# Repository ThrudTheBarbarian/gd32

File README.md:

# gd32
Test board for the GD32F450 cpu

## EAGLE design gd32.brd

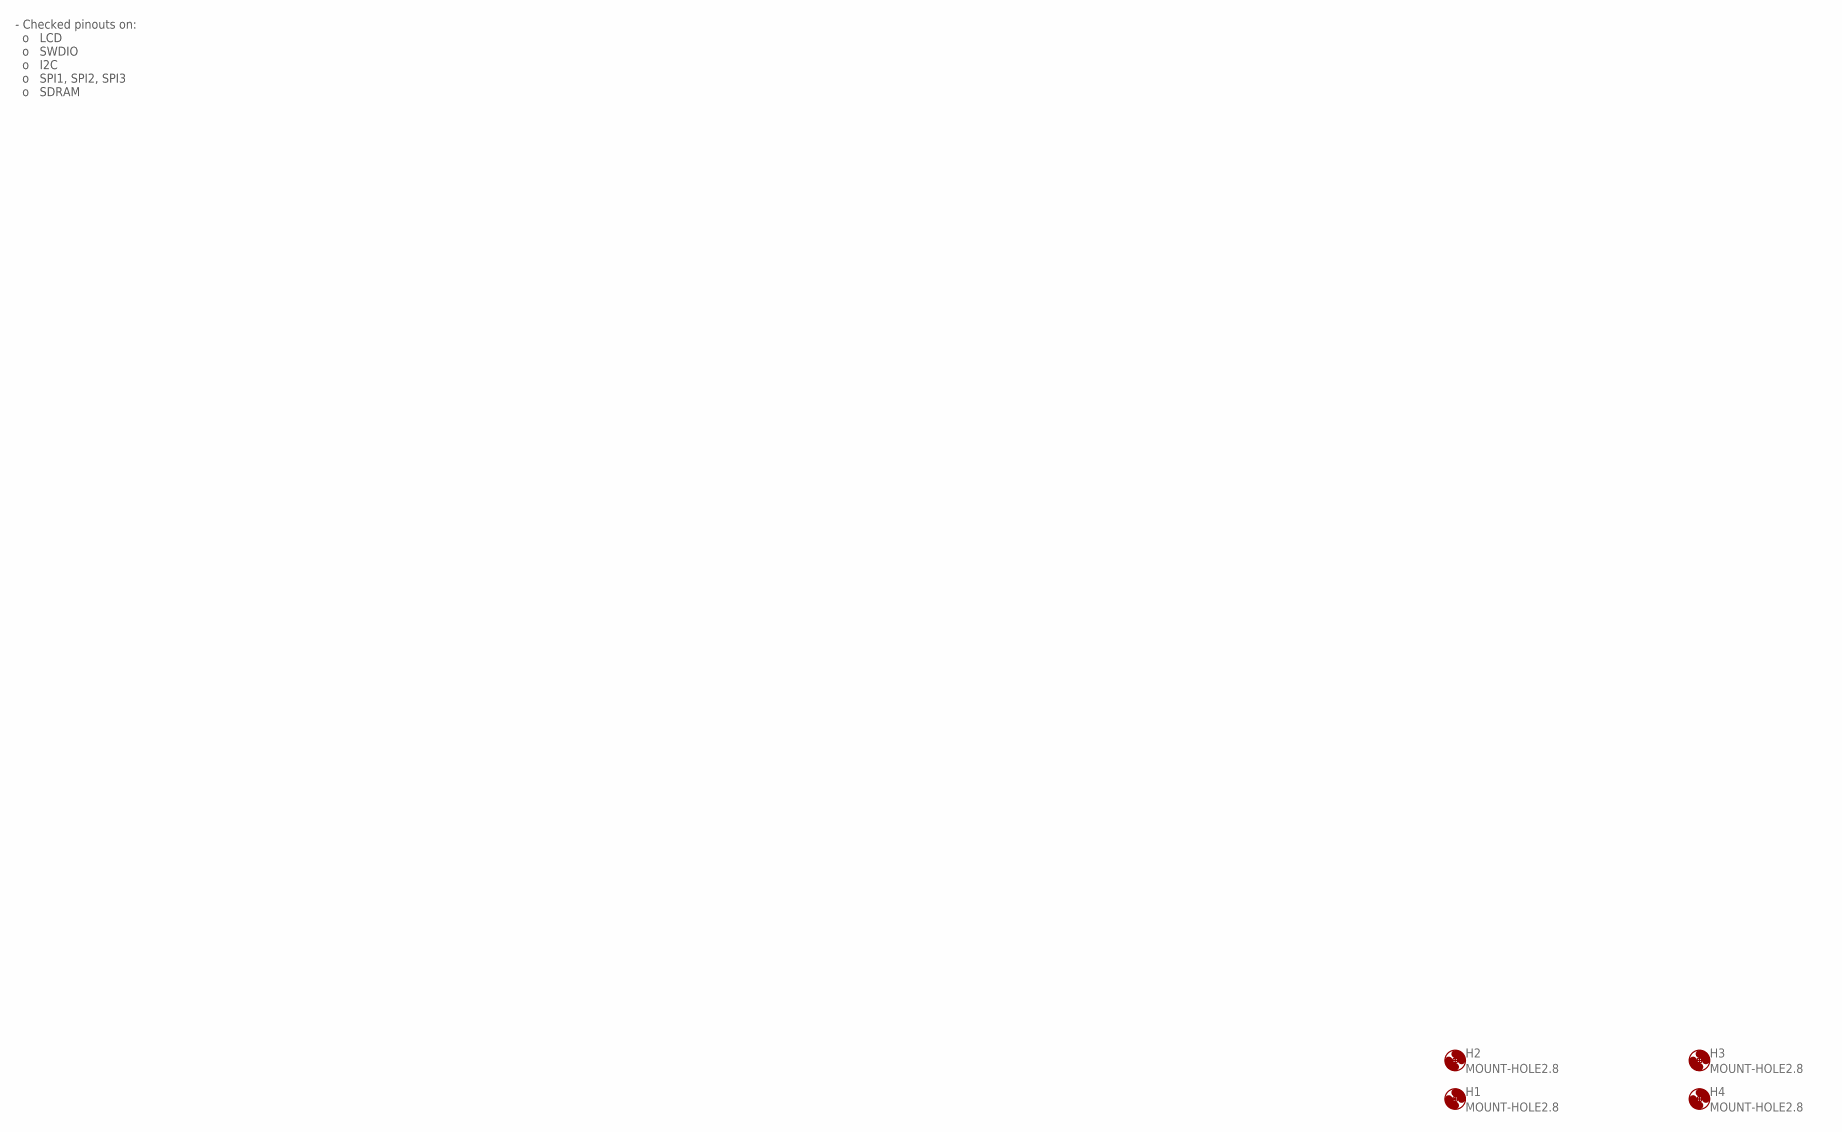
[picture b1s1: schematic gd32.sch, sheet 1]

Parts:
H1, H2, H3, H4: MOUNT-HOLE2.8; 2,8

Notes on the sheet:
- Checked pinouts on: o LCD o SWDIO o I2C o SPI1, SPI2, SPI3 o SDRAM

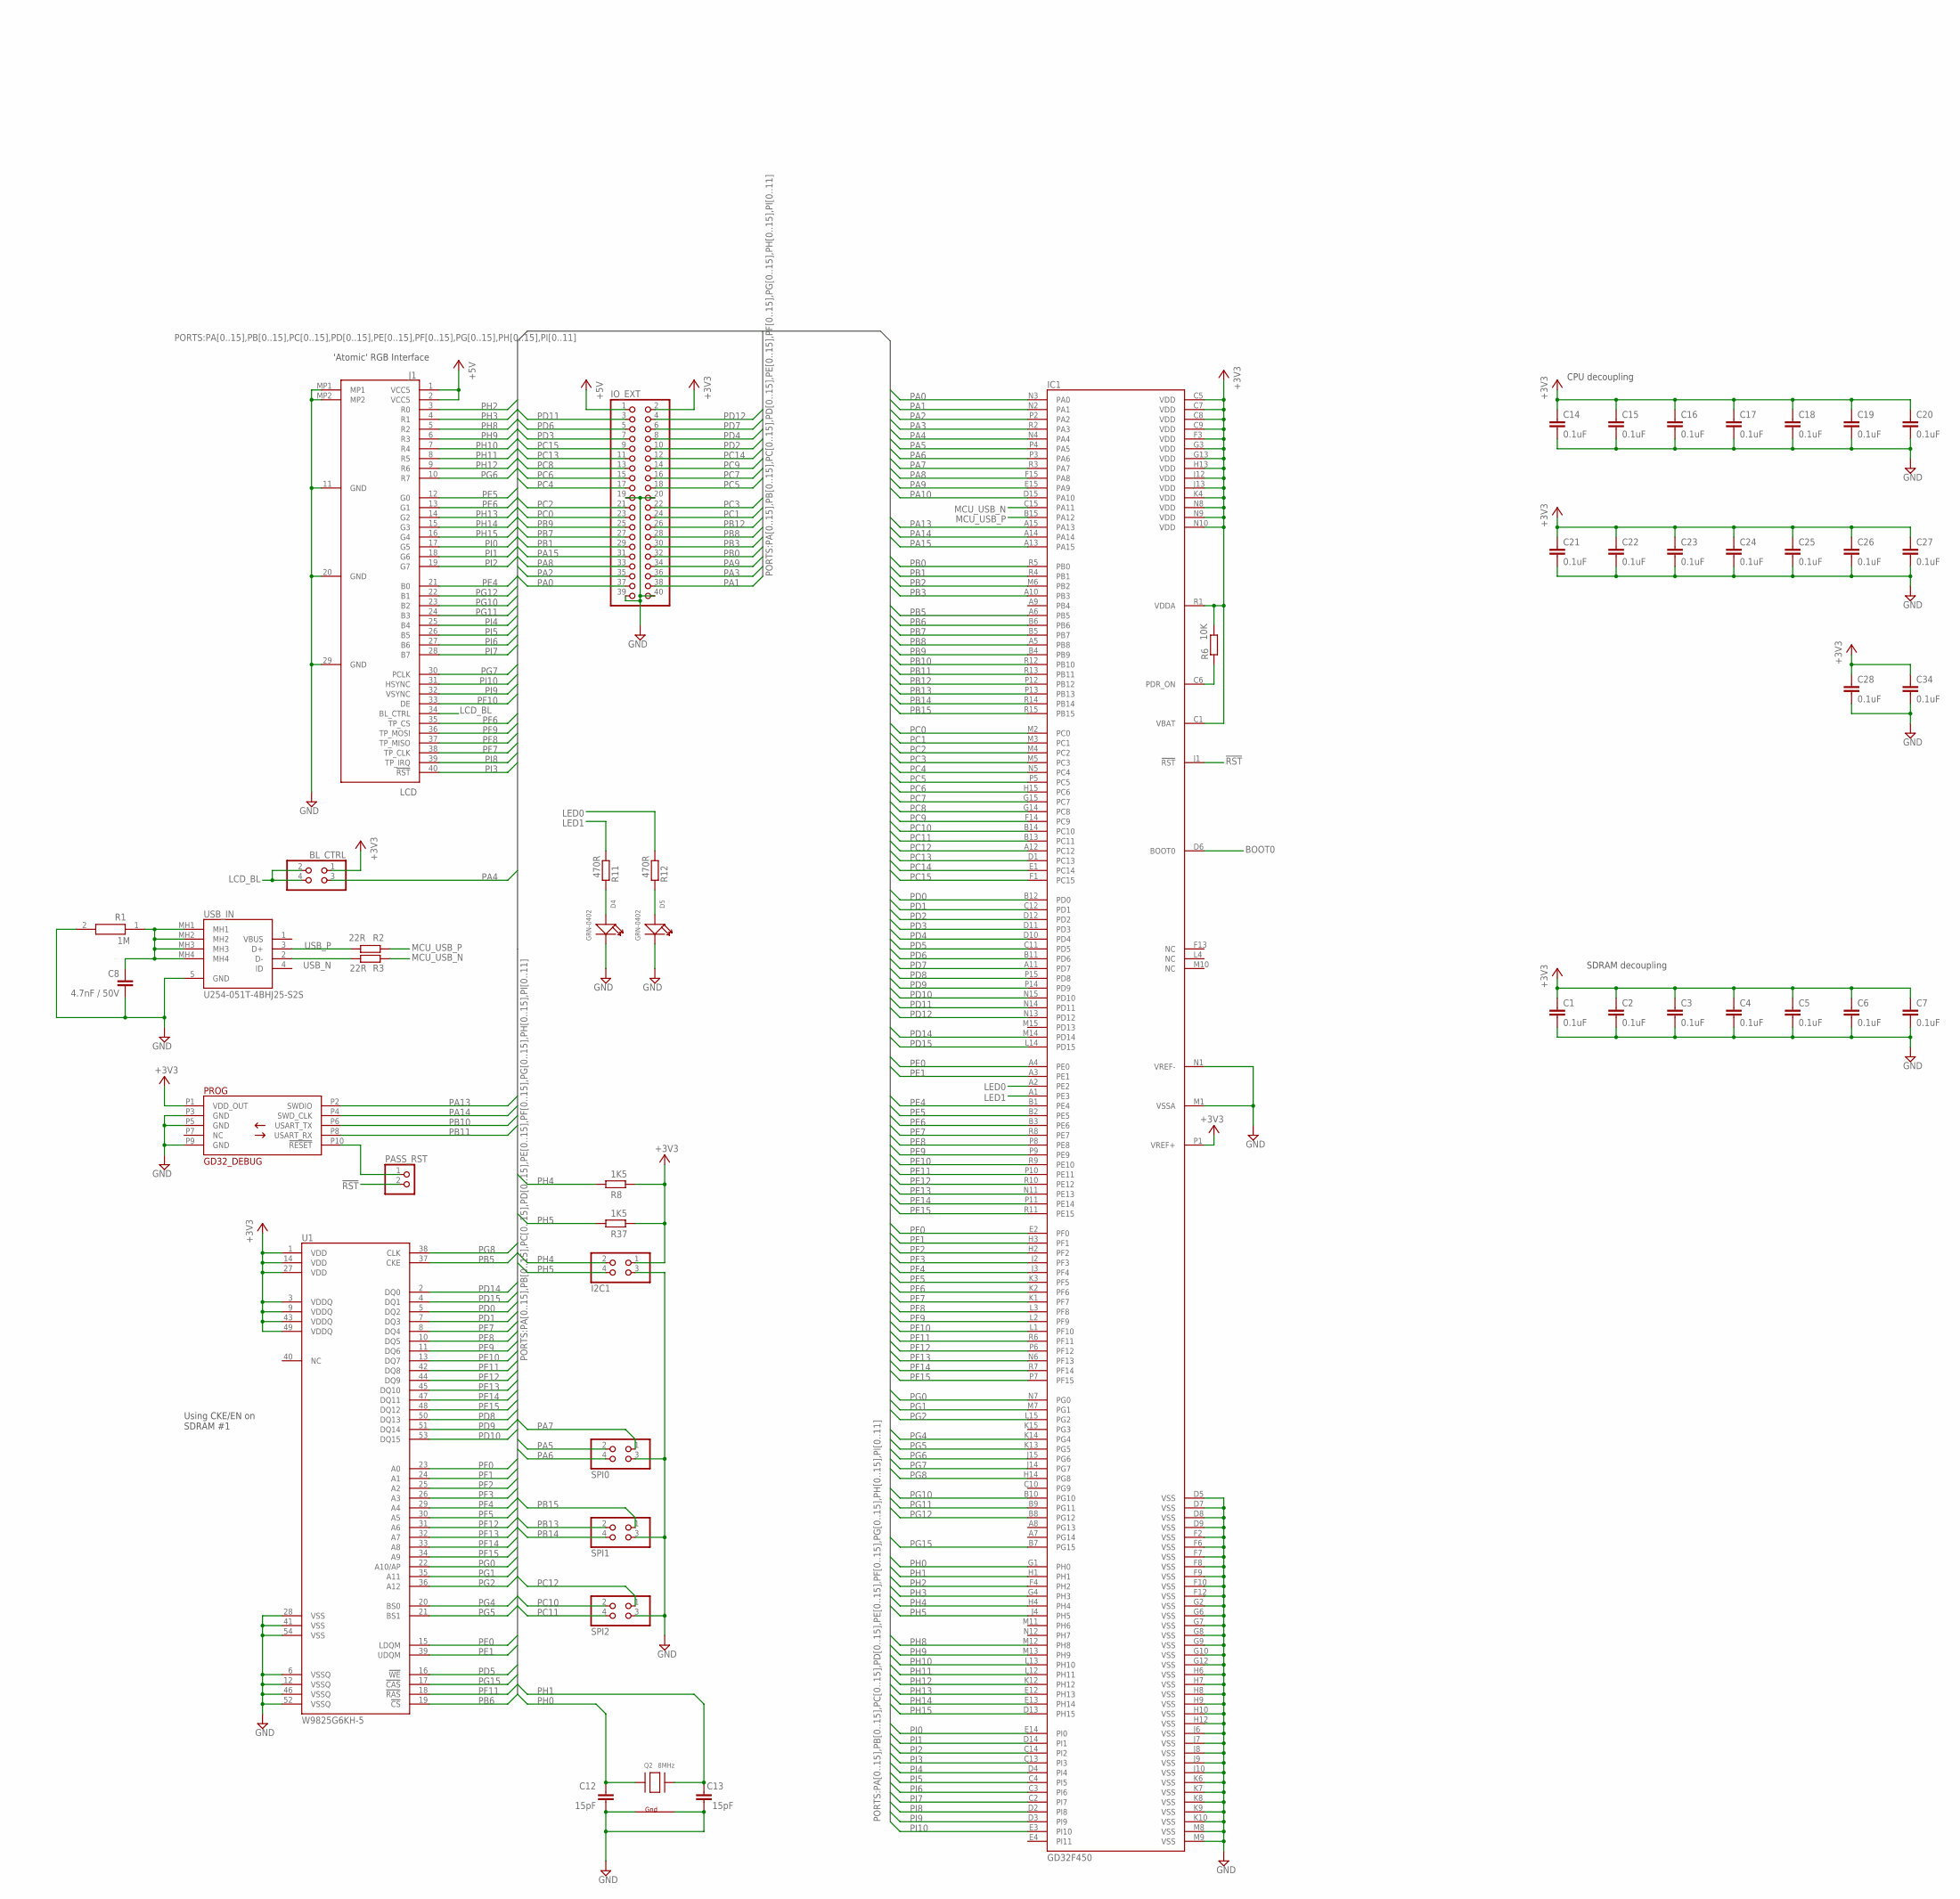
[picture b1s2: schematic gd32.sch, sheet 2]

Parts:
BL_CTRL: PINHD-2X2; 2X02
C1, C2, C3, C4, C5, C6, C7, C14, C15, C16, C17, C18, C19, C20, C21, C22, C23, C24, C25, C26, C27, C28, C34: 0.1uF; C0201
C8: 4.7nF / 50V; C0201
C12, C13: 15pF; C0201
D4, D5: GRN-0402; LED-0402
I2C1: PINHD-2X2; 2X02
IC1: GD32F450; BGA201C65P15X15_1000X1000X84
IO_EXT: PINHD-2X20; 2X20
J1: LCD; CF5040FD0R005NH
PASS_RST: PINHD-1X2; 1X02
PROG: GD32_DEBUG; SWD_DEBUG
Q2: 8MHz; NX3225
R1: 1M; ERJ1GN_(0201)
R2, R3: 22R; R0402
R6: 10K; R0402
R8, R37: 1K5; R0603
R11, R12: 470R; R0402
SPI0, SPI1, SPI2: PINHD-2X2; 2X02
U1: W9825G6KH-5; SOP80P1176X120-54N
USB_IN: U254-051T-4BHJ25-S2S; U254051T4BHJ25S2S

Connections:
!RST!: IC1.J1 (!RST!), PASS_RST.2; also elsewhere on the board
+3V3: BL_CTRL.1, C1.1, C2.1, C3.1, C4.1, C5.1, C6.1, C7.1, C14.1, C15.1, C16.1, C17.1, C18.1, C19.1, C20.1, C21.1, C22.1, C23.1, C24.1, C25.1, C26.1, C27.1, C28.1, C34.1, I2C1.1, IC1.C1 (VBAT), IC1.C5 (VDD), IC1.C7 (VDD), IC1.C8 (VDD), IC1.C9 (VDD), IC1.F3 (VDD), IC1.G3 (VDD), IC1.G13 (VDD), IC1.H13 (VDD), IC1.J12 (VDD), IC1.J13 (VDD), IC1.K4 (VDD), IC1.N8 (VDD), IC1.N9 (VDD), IC1.N10 (VDD), IC1.P1 (VREF+), IC1.R1 (VDDA), IO_EXT.2, PROG.P1 (VDD_OUT), R6.2, R8.2, R37.2, U1.1 (VDD), U1.3 (VDDQ), U1.9 (VDDQ), U1.14 (VDD), U1.27 (VDD), U1.43 (VDDQ), U1.49 (VDDQ); also elsewhere on the board
+5V: IO_EXT.1, J1.1 (VCC5), J1.2 (VCC5); also elsewhere on the board
BOOT0: IC1.D6 (BOOT0); also elsewhere on the board
GND: C1.2, C2.2, C3.2, C4.2, C5.2, C6.2, C7.2, C8.2, C12.2, C13.2, C14.2, C15.2, C16.2, C17.2, C18.2, C19.2, C20.2, C21.2, C22.2, C23.2, C24.2, C25.2, C26.2, C27.2, C28.2, C34.2, D4.-, D5.-, I2C1.3, IC1.D5 (VSS), IC1.D7 (VSS), IC1.D8 (VSS), IC1.D9 (VSS), IC1.F2 (VSS), IC1.F6 (VSS), IC1.F7 (VSS), IC1.F8 (VSS), IC1.F9 (VSS), IC1.F10 (VSS), IC1.F12 (VSS), IC1.G2 (VSS), IC1.G6 (VSS), IC1.G7 (VSS), IC1.G8 (VSS), IC1.G9 (VSS), IC1.G10 (VSS), IC1.G12 (VSS), IC1.H6 (VSS), IC1.H7 (VSS), IC1.H8 (VSS), IC1.H9 (VSS), IC1.H10 (VSS), IC1.H12 (VSS), IC1.J6 (VSS), IC1.J7 (VSS), IC1.J8 (VSS), IC1.J9 (VSS), IC1.J10 (VSS), IC1.K6 (VSS), IC1.K7 (VSS), IC1.K8 (VSS), IC1.K9 (VSS), IC1.K10 (VSS), IC1.M1 (VSSA), IC1.M8 (VSS), IC1.M9 (VSS), IC1.N1 (VREF-), IO_EXT.19, IO_EXT.20, IO_EXT.39, IO_EXT.40, J1.11 (GND), J1.20 (GND), J1.29 (GND), J1.MP1, J1.MP2, PROG.P3 (GND), PROG.P5 (GND), PROG.P9 (GND), Q2.2 (G2), Q2.4 (G1), R1.2, SPI0.3, SPI1.3, SPI2.3, U1.6 (VSSQ), U1.12 (VSSQ), U1.28 (VSS), U1.41 (VSS), U1.46 (VSSQ), U1.52 (VSSQ), U1.54 (VSS), USB_IN.5 (GND); also elsewhere on the board
LCD_BL: BL_CTRL.2, BL_CTRL.4, J1.34 (BL_CTRL)
LED0: IC1.A2 (PE2), R12.1
LED1: IC1.A1 (PE3), R11.1
MCU_USB_N: IC1.C15 (PA11), R3.1
MCU_USB_P: IC1.B15 (PA12), R2.1
unnamed: C8.1, R1.1, USB_IN.MH1, USB_IN.MH2, USB_IN.MH3, USB_IN.MH4
unnamed: IC1.C6 (PDR_ON), R6.1
unnamed: PASS_RST.1, PROG.P10 (!RESET!)
unnamed: D4.+, R11.2
unnamed: D5.+, R12.2
PA0: IC1.N3 (PA0), IO_EXT.37
PA1: IC1.N2 (PA1), IO_EXT.38
PA2: IC1.P2 (PA2), IO_EXT.35
PA3: IC1.R2 (PA3), IO_EXT.36
PA4: BL_CTRL.3, IC1.N4 (PA4)
PA5: IC1.P4 (PA5), SPI0.2
PA6: IC1.P3 (PA6), SPI0.4
PA7: IC1.R3 (PA7), SPI0.1
PA8: IC1.F15 (PA8), IO_EXT.33
PA9: IC1.E15 (PA9), IO_EXT.34
PA10: IC1.D15 (PA10)
PA13: IC1.A15 (PA13), PROG.P2 (SWDIO)
PA14: IC1.A14, PROG.P4 (SWD_CLK)
PA15: IC1.A13 (PA15), IO_EXT.31
PB0: IC1.R5 (PB0), IO_EXT.32
PB1: IC1.R4 (PB1), IO_EXT.29
PB2: IC1.M6 (PB2); also elsewhere on the board
PB3: IC1.A10 (PB3), IO_EXT.30
PB5: IC1.A6 (PB5), U1.37 (CKE)
PB6: IC1.B6, U1.19 (!CS)
PB7: IC1.B5 (PB7), IO_EXT.27
PB8: IC1.A5 (PB8), IO_EXT.28
PB9: IC1.B4 (PB9), IO_EXT.25
PB10: IC1.R12 (PB10), PROG.P6 (USART_TX)
PB11: IC1.R13 (PB11), PROG.P8 (USART_RX)
PB12: IC1.P12 (PB12), IO_EXT.26
PB13: IC1.P13 (PB13), SPI1.2
PB14: IC1.R14 (PB14), SPI1.4
PB15: IC1.R15 (PB15), SPI1.1
PC0: IC1.M2 (PC0), IO_EXT.23
PC1: IC1.M3 (PC1), IO_EXT.24
PC2: IC1.M4 (PC2), IO_EXT.21
PC3: IC1.M5 (PC3), IO_EXT.22
PC4: IC1.N5 (PC4), IO_EXT.17
PC5: IC1.P5 (PC5), IO_EXT.18
PC6: IC1.H15 (PC6), IO_EXT.15
PC7: IC1.G15 (PC7), IO_EXT.16
PC8: IC1.G14 (PC8), IO_EXT.13
PC9: IC1.F14 (PC9), IO_EXT.14
PC10: IC1.B14 (PC10), SPI2.2
PC11: IC1.B13 (PC11), SPI2.4
PC12: IC1.A12 (PC12), SPI2.1
PC13: IC1.D1 (PC13), IO_EXT.11
PC14: IC1.E1 (PC14), IO_EXT.12
PC15: IC1.F1 (PC15), IO_EXT.9
PD0: IC1.B12 (PD0), U1.5 (DQ2)
PD1: IC1.C12 (PD1), U1.7 (DQ3)
PD2: IC1.D12 (PD2), IO_EXT.10
PD3: IC1.D11 (PD3), IO_EXT.7
PD4: IC1.D10 (PD4), IO_EXT.8
PD5: IC1.C11 (PD5), U1.16 (!WE)
PD6: IC1.B11 (PD6), IO_EXT.5
PD7: IC1.A11 (PD7), IO_EXT.6
PD8: IC1.P15 (PD8), U1.50 (DQ13)
PD9: IC1.P14 (PD9), U1.51 (DQ14)
PD10: IC1.N15 (PD10), U1.53 (DQ15)
PD11: IC1.N14 (PD11), IO_EXT.3
PD12: IC1.N13 (PD12), IO_EXT.4
PD14: IC1.M14 (PD14), U1.2 (DQ0)
PD15: IC1.L14 (PD15), U1.4 (DQ1)
PE0: IC1.A4 (PE0), U1.15 (LDQM)
PE1: IC1.A3 (PE1), U1.39 (UDQM)
PE4: IC1.B1 (PE4), J1.21 (B0)
PE5: IC1.B2 (PE5), J1.12 (G0)
PE6: IC1.B3 (PE6), J1.13 (G1)
PE7: IC1.R8 (PE7), U1.8 (DQ4)
PE8: IC1.P8 (PE8), U1.10 (DQ5)
PE9: IC1.P9 (PE9), U1.11 (DQ6)
PE10: IC1.R9 (PE10), U1.13 (DQ7)
PE11: IC1.P10 (PE11), U1.42 (DQ8)
PE12: IC1.R10 (PE12), U1.44 (DQ9)
PE13: IC1.N11 (PE13), U1.45 (DQ10)
PE14: IC1.P11 (PE14), U1.47 (DQ11)
PE15: IC1.R11 (PE15), U1.48 (DQ12)
PF0: IC1.E2 (PF0), U1.23 (A0)
PF1: IC1.H3 (PF1), U1.24 (A1)
PF2: IC1.H2 (PF2), U1.25 (A2)
PF3: IC1.J2 (PF3), U1.26 (A3)
PF4: IC1.J3 (PF4), U1.29 (A4)
PF5: IC1.K3 (PF5), U1.30 (A5)
PF6: IC1.K2 (PF6), J1.35 (TP_CS)
PF7: IC1.K1 (PF7), J1.38 (TP_CLK)
PF8: IC1.L3 (PF8), J1.37 (TP_MISO)
PF9: IC1.L2 (PF9), J1.36 (TP_MOSI)
PF10: IC1.L1 (PF10), J1.33 (DE)
PF11: IC1.R6 (PF11), U1.18 (!RAS)
PF12: IC1.P6 (PF12), U1.31 (A6)
PF13: IC1.N6 (PF13), U1.32 (A7)
PF14: IC1.R7 (PF14), U1.33 (A8)
PF15: IC1.P7 (PF15), U1.34 (A9)
PG0: IC1.N7 (PG0), U1.22 (A10/AP)
PG1: IC1.M7 (PG1), U1.35 (A11)
PG2: IC1.L15 (PG2), U1.36 (A12)
PG4: IC1.K14 (PG4), U1.20 (BS0)
PG5: IC1.K13 (PG5), U1.21 (BS1)
PG6: IC1.J15 (PG6), J1.10 (R7)
PG7: IC1.J14 (PG7), J1.30 (PCLK)
PG8: IC1.H14 (PG8), U1.38 (CLK)
PG10: IC1.B10 (PG10), J1.23 (B2)
PG11: IC1.B9 (PG11), J1.24 (B3)
PG12: IC1.B8 (PG12), J1.22 (B1)
PG15: IC1.B7 (PG15), U1.17 (!CAS)
PH0: C12.1, IC1.G1 (PH0), Q2.1 (X1)
PH1: C13.1, IC1.H1, Q2.3 (X2)
PH2: IC1.F4 (PH2), J1.3 (R0)
PH3: IC1.G4 (PH3), J1.4 (R1)
PH4: I2C1.2, IC1.H4, R8.1
PH5: I2C1.4, IC1.J4 (PH5), R37.1
PH8: IC1.M12 (PH8), J1.5 (R2)
PH9: IC1.M13 (PH9), J1.6 (R3)
PH10: IC1.L13 (PH10), J1.7 (R4)
PH11: IC1.L12 (PH11), J1.8 (R5)
PH12: IC1.K12 (PH12), J1.9 (R6)
PH13: IC1.E12 (PH13), J1.14 (G2)
PH14: IC1.E13 (PH14), J1.15 (G3)
PH15: IC1.D13 (PH15), J1.16 (G4)
PI0: IC1.E14 (PI0), J1.17 (G5)
PI1: IC1.D14 (PI1), J1.18 (G6)
PI2: IC1.C14 (PI2), J1.19 (G7)
PI3: IC1.C13 (PI3), J1.40 (!RST!)
PI4: IC1.D4 (PI4), J1.25 (B4)
PI5: IC1.C4 (PI5), J1.26 (B5)
PI6: IC1.C3 (PI6), J1.27 (B6)
PI7: IC1.C2 (PI7), J1.28 (B7)
PI8: IC1.D2 (PI8), J1.39 (TP_IRQ)
PI9: IC1.D3 (PI9), J1.32 (VSYNC)
PI10: IC1.E3 (PI10), J1.31 (HSYNC)
USB_N: R3.2, USB_IN.2 (D-)
USB_P: R2.2, USB_IN.3 (D+)

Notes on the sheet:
'Atomic' RGB Interface
Using CKE/EN on SDRAM #1
SDRAM decoupling
CPU decoupling

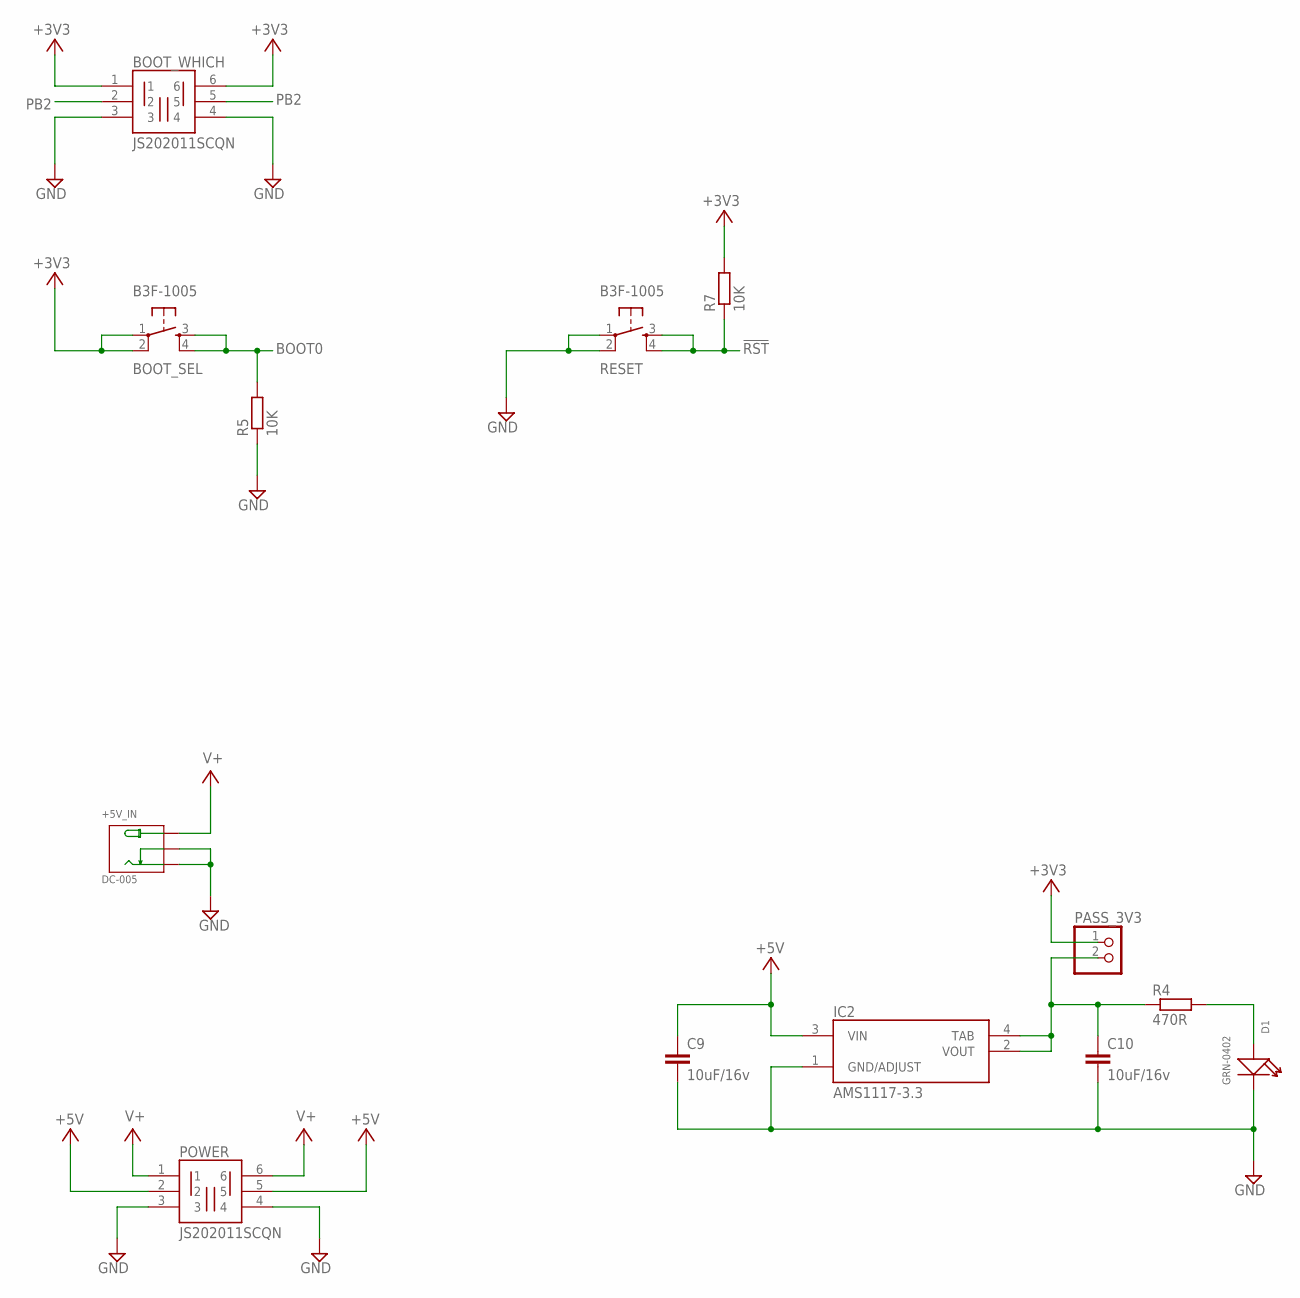
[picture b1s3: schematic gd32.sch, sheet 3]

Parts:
+5V_IN: DC-005; DCJ3P-14.2X11.0X9.0MM
BOOT_SEL: B3F-1005; TACTILE-PTH
BOOT_WHICH: JS202011SCQN
C9, C10: 10uF/16v; C0603
D1: GRN-0402; LED-0402
IC2: AMS1117-3.3; SOT229P700X180-4N
PASS_3V3: PINHD-1X2; 1X02
POWER: JS202011SCQN
R4: 470R; R0402
R5, R7: 10K; R0402
RESET: B3F-1005; TACTILE-PTH

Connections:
!RST!: R7.1, RESET.3, RESET.4; also elsewhere on the board
+3V3: BOOT_SEL.1, BOOT_SEL.2, BOOT_WHICH.1, BOOT_WHICH.6, PASS_3V3.1, R7.2; also elsewhere on the board
+5V: C9.1, IC2.3 (VIN), POWER.2, POWER.5; also elsewhere on the board
BOOT0: BOOT_SEL.3, BOOT_SEL.4, R5.2; also elsewhere on the board
GND: +5V_IN.-1 (-), +5V_IN.-2 (CDN), BOOT_WHICH.3, BOOT_WHICH.4, C9.2, C10.2, D1.-, IC2.1 (GND/ADJUST), POWER.3, POWER.4, R5.1, RESET.1, RESET.2; also elsewhere on the board
unnamed: D1.+, R4.2
unnamed: C10.1, IC2.2 (VOUT), IC2.4 (TAB), PASS_3V3.2, R4.1
PB2: BOOT_WHICH.2, BOOT_WHICH.5; also elsewhere on the board
V+: +5V_IN.+, POWER.1, POWER.6

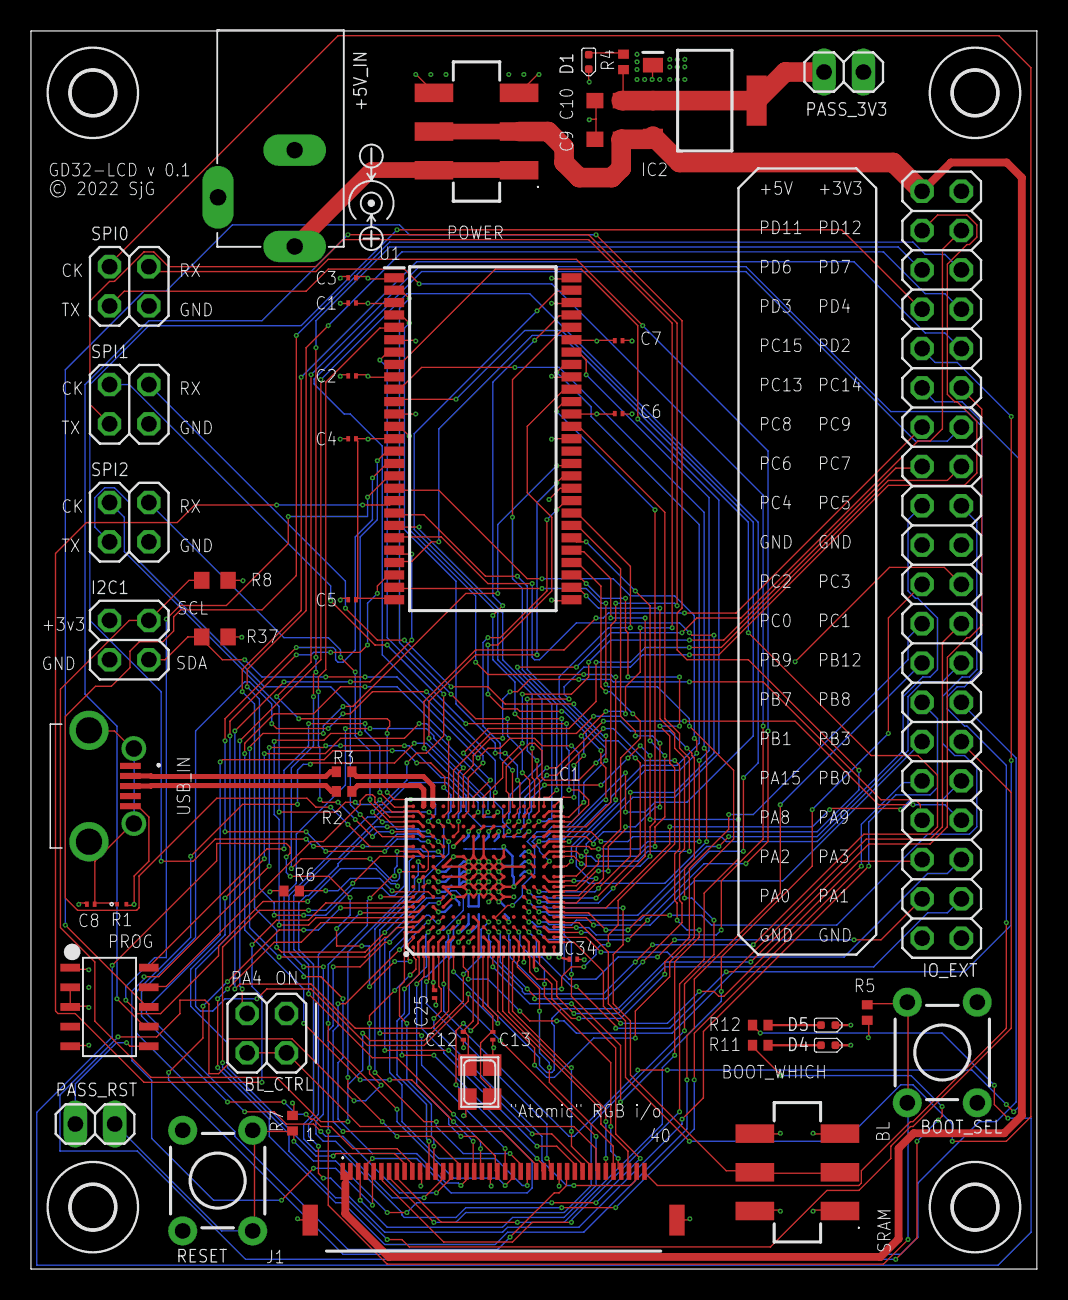
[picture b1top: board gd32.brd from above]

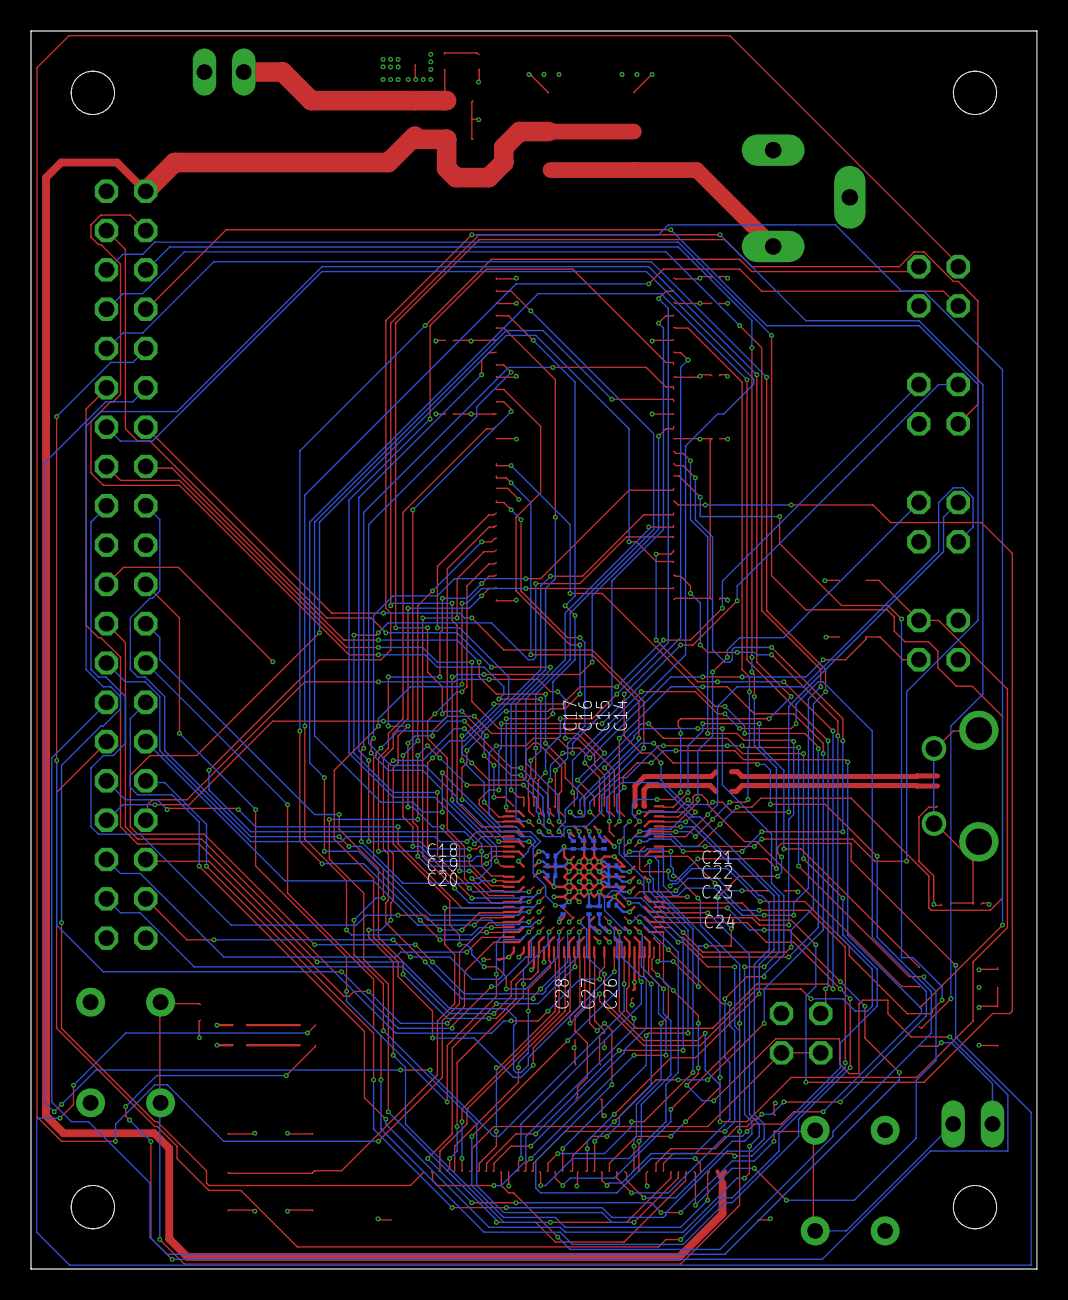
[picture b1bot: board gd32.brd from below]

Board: 4 copper layers, 65.0 x 80.0 mm, 66 parts (14 on the bottom side), 146 nets.

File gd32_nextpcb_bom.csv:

ID,Name,Designator,Package,Quantity,Manufacturer Part,Manufacturer,Supplier,Supplier Part,Mounted,Stock
1,PINHD-1X2,"PASS_3V3, PASS_RST",1x02,2,PZ254V-11-02P,XFCN,LCSC,C492401,Yes,172800
2,PINHD-2x2,"BL_CTRL, I2C1, SPI0, SPI1, SPI2",2x02,5,C66690,Boom Precision Elec,LCSC,C66690,Yes,42800
3,PINHD-2x20,IO_EXT,2x20,1,12251220ANG0S115001,JILN,LCSC,C429965,Yes,10290
4,0.1uF,"C1, C2, C3, C4, C5, C6, C7, C14, C15, C16, C17, C18, C19, C20, C21, C22, C23, C24, C25, C26, C27, C28, C34",C0201,23,GRM033R61A104ME15D,Murata Electronics,Digi-Key,490-5405-1-ND,Yes,6642703
5,10K,"R5, R6, R7",R0402,3,CR0402-JW-103GLF,Bourns Inc,Digi-Key,CR0402-JW-103GLFCT-ND,Yes,738885
6,10uF/16v,"C9, C10",C0603,2,GRM188R61C106MA73D,Murata Electronics,Digi-Key,490-7201-1-ND,Yes,257364
7,15pF,"C12, C13",C0201,2,0201N150J500CT,Walsin Technology Corp,Digi-Key,1292-1139-1-ND,Yes,47030
8,1K5,"R8, R37",R0603,2,WR06X152 JTL,Walsin Technology Corp,Digi-Key,1292-WR06X152JTLCT-ND,Yes,23148
9,1M,R1,R0201,1,RC0201FR-071ML,Yageo,Digi-Key,311-1MMCT-ND,Yes,991318
10,22R,"R2, R3",R0402,2,CR0402-JW-220GLF,Bourns Inc,Digi-Key,CR0402-JW-220GLFCT-ND,Yes,72781
11,4.7nF / 50V,C8,C0201,1,UMK063BJ472MP-F,Taiyo Yuden,Digi-Key,587-UMK063BJ472MP-FCT-ND,Yes,14371
12,470R,"R4,R11,R12",R0402,3,CR0402-FX-4700GLF,Bourns Inc,Digi-Key,CR0402-FX-4700GLFCT-ND,Yes,18615
13,8MHz,Q2,NX3225,1,ECS-80-10-33-CHN-TR,ECS Inc,Digi-Key,50-ECS-80-10-33-CHN-CT-ND,Yes,7388
14,AMS1117-3.3,IC2,SOT23,1,AMS1117-3.3,UMW (Youtai Semiconductor Co.),LCSC,C347222,Yes,1237120
15,B3F-1005,"BOOT_SEL, RESET",TACTILE-PTH,2,B3F-1005,Omron Electronics,LCSC,C397293,Yes,1639
16,DC-005,+5V_IN,DCJ3P-14.2X11.0X9.0MM,1,DC-005 2.0,Boom Precision Elec,LCSC,C16214,Yes,96880
17,GD32F450,IC1,BGA176,1,GD32F450IIH6,Gigadevice Semicon,LCSC,C179655,Yes,37
18,GD32_DEBUG,PROG,SMD-10-1.27,1,FTSH-105-01-LM-DV-K-P-TR,"Samtec, Inc",Digi-Key,SAM13168CT-ND,Yes,13509
21,GRN-0402,"D1,D4,D5",LED-0402,3,IN-S42BT5G,Inolux,Digi-Key,1830-IN-S42BT5GCT-ND,Yes,48440
22,JS202011SCQN,"BOOT_WHICH, POWER",JS202011SCQN,2,JS202011SCQN,C&K,LCSC,C221666,Yes,1934
23,LCD,J1,FFC40,1,CF5040FD0R0-05-NH,Cvilux USA,Digi-Key,2987-CF5040FD0R0-05-NHCT-ND,Yes,2974
25,USB,USB_IN,U254051T4BHJ25S2S,1,U254-051T-4BHJ25-S2S,XKB Connectivity,LCSC,C319163,Yes,83460
24,SDRAM,U1,TSOP-54,1,W9825G6KH-6I,Winbond Elec,LCSC,C97572,Yes,258
25,,,,,,,,,,
19,,,,,,,,,,
20,,,,,,,,,,

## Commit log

2022-06-08 Initial import
2022-06-08 Incremental changes
2022-06-09 Ready for manufacture
2022-06-09 Add the bom and the pin-map
2022-06-11 Sent off for manufacture, with corrected 1K5 pullups on I2C
2022-06-11 Persist the correct new pullup parts in the USE tags of the schematic components
2022-06-11 Add a PDF for when Eagle expires...
2022-06-17 Alter the pad sizes in the GD32 library

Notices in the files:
gd32.brd:
© 2022 SjG
parts and their libraries:
SparkFun: Licensing: CC v3.0 Share-Alike You are welcome to use this library for commercial purposes.
